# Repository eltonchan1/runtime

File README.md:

# \#runtime - a PCB that converts rotational position into frequency

# Components

For my input, I rolled the AS5600, which gives the exact rotational position of the PCB.
For my output, I rolled a Passive piezo buzzer, which buzzes when you run a signal through it.
For my connector, I rolled a Carabiner, which is added on through the hole in the PCB.
I chose to use the Seeed Studio XIAO RP2040 for my microcontroller because it was beginner friendly and easy to use.

# Function

When powered, the PCB will buzz from the buzzer, and based on the rotational position read by the AS5600, the buzzer will buzz at a different frequency.

# Screenshots

Schematic:

PCB:

# Bill of Materials

| Part                          | Qty | Source          | Total Cost $USD |
|-------------------------------|-----|-----------------|-----------------|
| XIAO RP2040                   | 1   | Seeed Studio    | $3.90           |
| AS5600 Magnetic angle sensor  | 1   | JLCPCB catalog  | $1.41           |
| 4.7k resistor                 | 2   | JLCPCB catalog  | $0.02           |
| Passive piezo buzzer          | 1   | JLCPCB catalog  | $0.22           |
| Total Cost                    | n/a | n/a             | $5.55           |

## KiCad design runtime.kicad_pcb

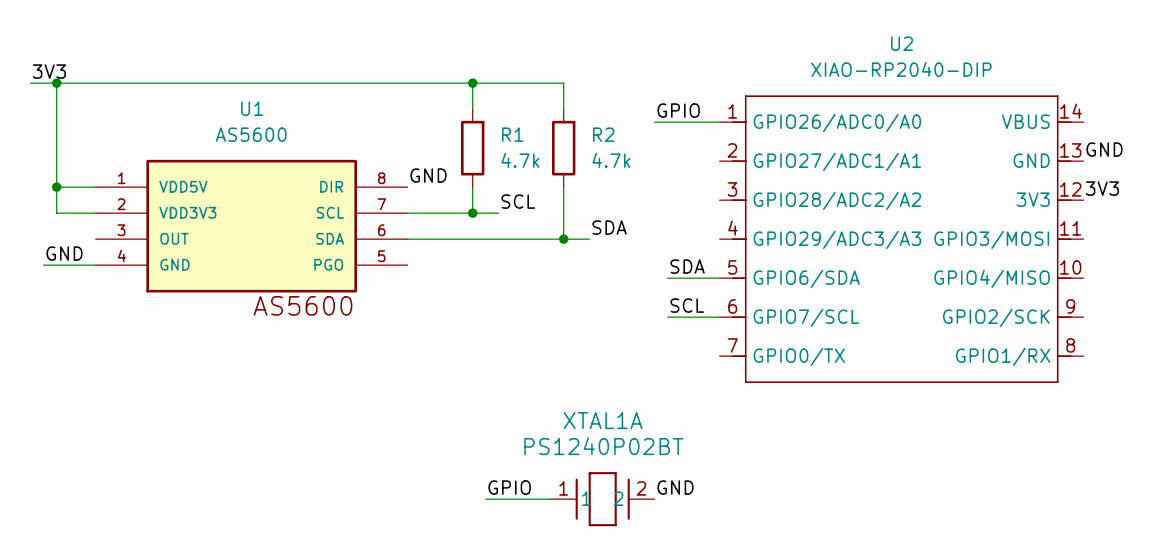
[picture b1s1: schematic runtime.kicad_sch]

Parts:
R1, R2: 4.7k; R_0603_1608Metric
U1: AS5600; SOIC-8_3.9x4.9mm_P1.27mm
U2: XIAO-RP2040-DIP; MCU_Seeed_ESP32C3
XTAL1: PS1240P02BT; Buzzer_TDK_PS1240P02BT_D12.2mm_H6.5mm

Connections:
/3V3: R1.2, R2.2, U1.1 (VDD5V), U1.2 (VDD3V3), U2.12 (3V3)
/GND: U1.4 (GND), U1.8 (DIR), U2.13 (GND), XTAL1.2
/GPIO: U2.1 (GPIO26/ADC0/A0), XTAL1.1
/SCL: R1.1, U1.7 (SCL), U2.6 (GPIO7/SCL)
/SDA: R2.1, U1.6 (SDA), U2.5 (GPIO6/SDA)

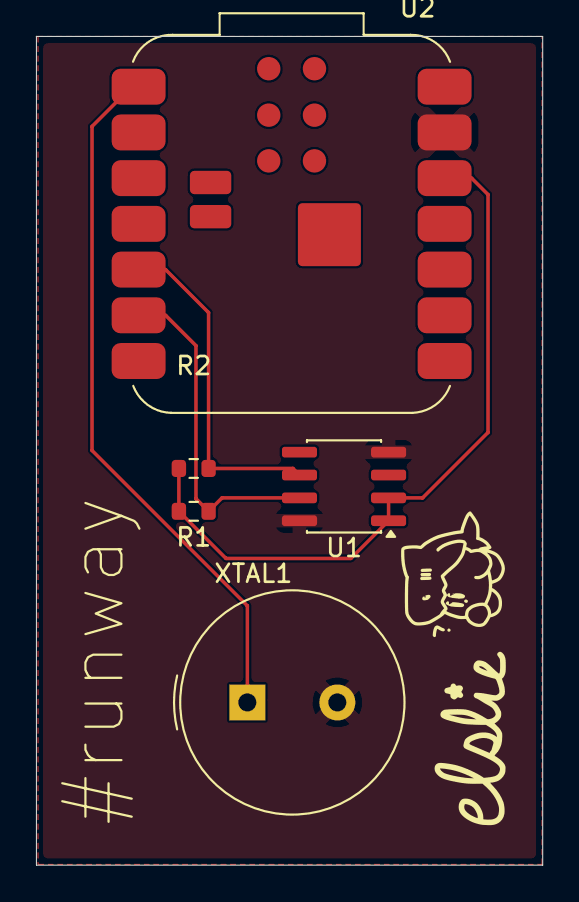
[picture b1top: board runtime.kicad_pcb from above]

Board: 2 copper layers, 28.1 x 46.0 mm, 5 parts (0 on the bottom side), 5 nets.
